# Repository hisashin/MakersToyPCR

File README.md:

## [We're fighting with COVID-19 by upgrading NinjaPCR into affordable Real-Time PCR.](https://github.com/hisashin/NinjaPCR/wiki/NinjaPCR's-fight-with-COVID-19)

NinjaPCR is Opensource(GPLv3) DNA Amplifier,Thermocycler Implementation for [Polymerase Chain Reaction](http://en.wikipedia.org/wiki/Polymerase_chain_reaction) developed by [Shingo Hisakawa](https://www.facebook.com/hisakawa) and [Mariko Hisakawa](https://www.facebook.com/maripo).<br />

Check [support site](https://ninjapcr.tori.st) for more infomations including how to [make](https://ninjapcr.tori.st/maker/) it. BOM is [here](https://docs.google.com/spreadsheets/d/1QYWESJrQ2N63OPvq1pnQvB-iVQkymN-hYeTYLx7xuOw/edit?usp=sharing).

Forked from [OpenPCR](https://github.com/jperfetto/OpenPCR).

Major changes from OpenPCR:<br />
01. Smaller and [easier to build](https://ninjapcr.tori.st/assy/index.html)<br />
02. Change platform from Adobe AIR to WiFi. Almost all PC and smartphones are supported<br />
03. LCD removed. Everything on Browser<br />
04. Keep precision from low to high temperature<br />
05. Auto update for new features (ex. IFTTT support scheduled)<br />
06. It's still [on sale](https://shop.tori.st) (OpenPCR is [discontinued](https://www.chaibio.com/openpcr))

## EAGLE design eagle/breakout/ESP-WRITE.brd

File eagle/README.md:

NinjaPCR PCB
============
[BOM is here](https://docs.google.com/spreadsheets/d/1Eu-5YibDgaByIjIB5OE9yRJ3uC1ED0U484PYJb1YKqg/edit#gid=36)

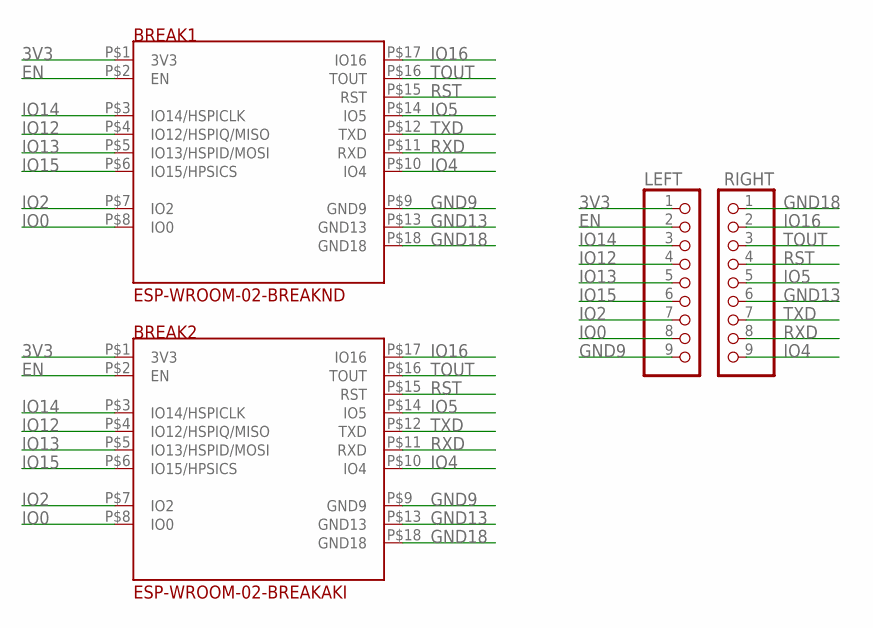
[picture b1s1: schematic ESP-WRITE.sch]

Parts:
BREAK1: ESP-WROOM-02-BREAKND; ESP-WROOM-02-BREAK-NODETAIL
BREAK2: ESP-WROOM-02-BREAKAKI; ESP-WROOM-02-AKI
LEFT: PINHD-1X9; 1X09
RIGHT: PINHD-1X9; 1X09

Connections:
3V3: BREAK1.P$1 (3V3), BREAK2.P$1 (3V3), LEFT.1
EN: BREAK1.P$2 (EN), BREAK2.P$2 (EN), LEFT.2
GND9: BREAK1.P$9 (GND9), BREAK2.P$9 (GND9), LEFT.9
GND13: BREAK1.P$13 (GND13), BREAK2.P$13 (GND13), RIGHT.6
GND18: BREAK1.P$18 (GND18), BREAK2.P$18 (GND18), RIGHT.1
IO0: BREAK1.P$8 (IO0), BREAK2.P$8 (IO0), LEFT.8
IO2: BREAK1.P$7 (IO2), BREAK2.P$7 (IO2), LEFT.7
IO4: BREAK1.P$10 (IO4), BREAK2.P$10 (IO4), RIGHT.9
IO5: BREAK1.P$14 (IO5), BREAK2.P$14 (IO5), RIGHT.5
IO12: BREAK1.P$4 (IO12/HSPIQ/MISO), BREAK2.P$4 (IO12/HSPIQ/MISO), LEFT.4
IO13: BREAK1.P$5 (IO13/HSPID/MOSI), BREAK2.P$5 (IO13/HSPID/MOSI), LEFT.5
IO14: BREAK1.P$3 (IO14/HSPICLK), BREAK2.P$3 (IO14/HSPICLK), LEFT.3
IO15: BREAK1.P$6 (IO15/HPSICS), BREAK2.P$6 (IO15/HPSICS), LEFT.6
IO16: BREAK1.P$17 (IO16), BREAK2.P$17 (IO16), RIGHT.2
RST: BREAK1.P$15 (RST), BREAK2.P$15 (RST), RIGHT.4
RXD: BREAK1.P$11 (RXD), BREAK2.P$11 (RXD), RIGHT.8
TOUT: BREAK1.P$16 (TOUT), BREAK2.P$16 (TOUT), RIGHT.3
TXD: BREAK1.P$12 (TXD), BREAK2.P$12 (TXD), RIGHT.7

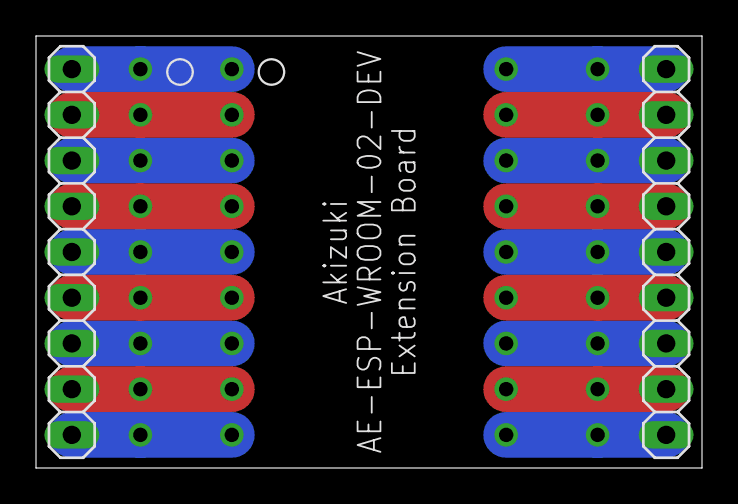
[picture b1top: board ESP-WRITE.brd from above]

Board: 2 copper layers, 37.0 x 24.0 mm, 4 parts (0 on the bottom side), 18 nets.

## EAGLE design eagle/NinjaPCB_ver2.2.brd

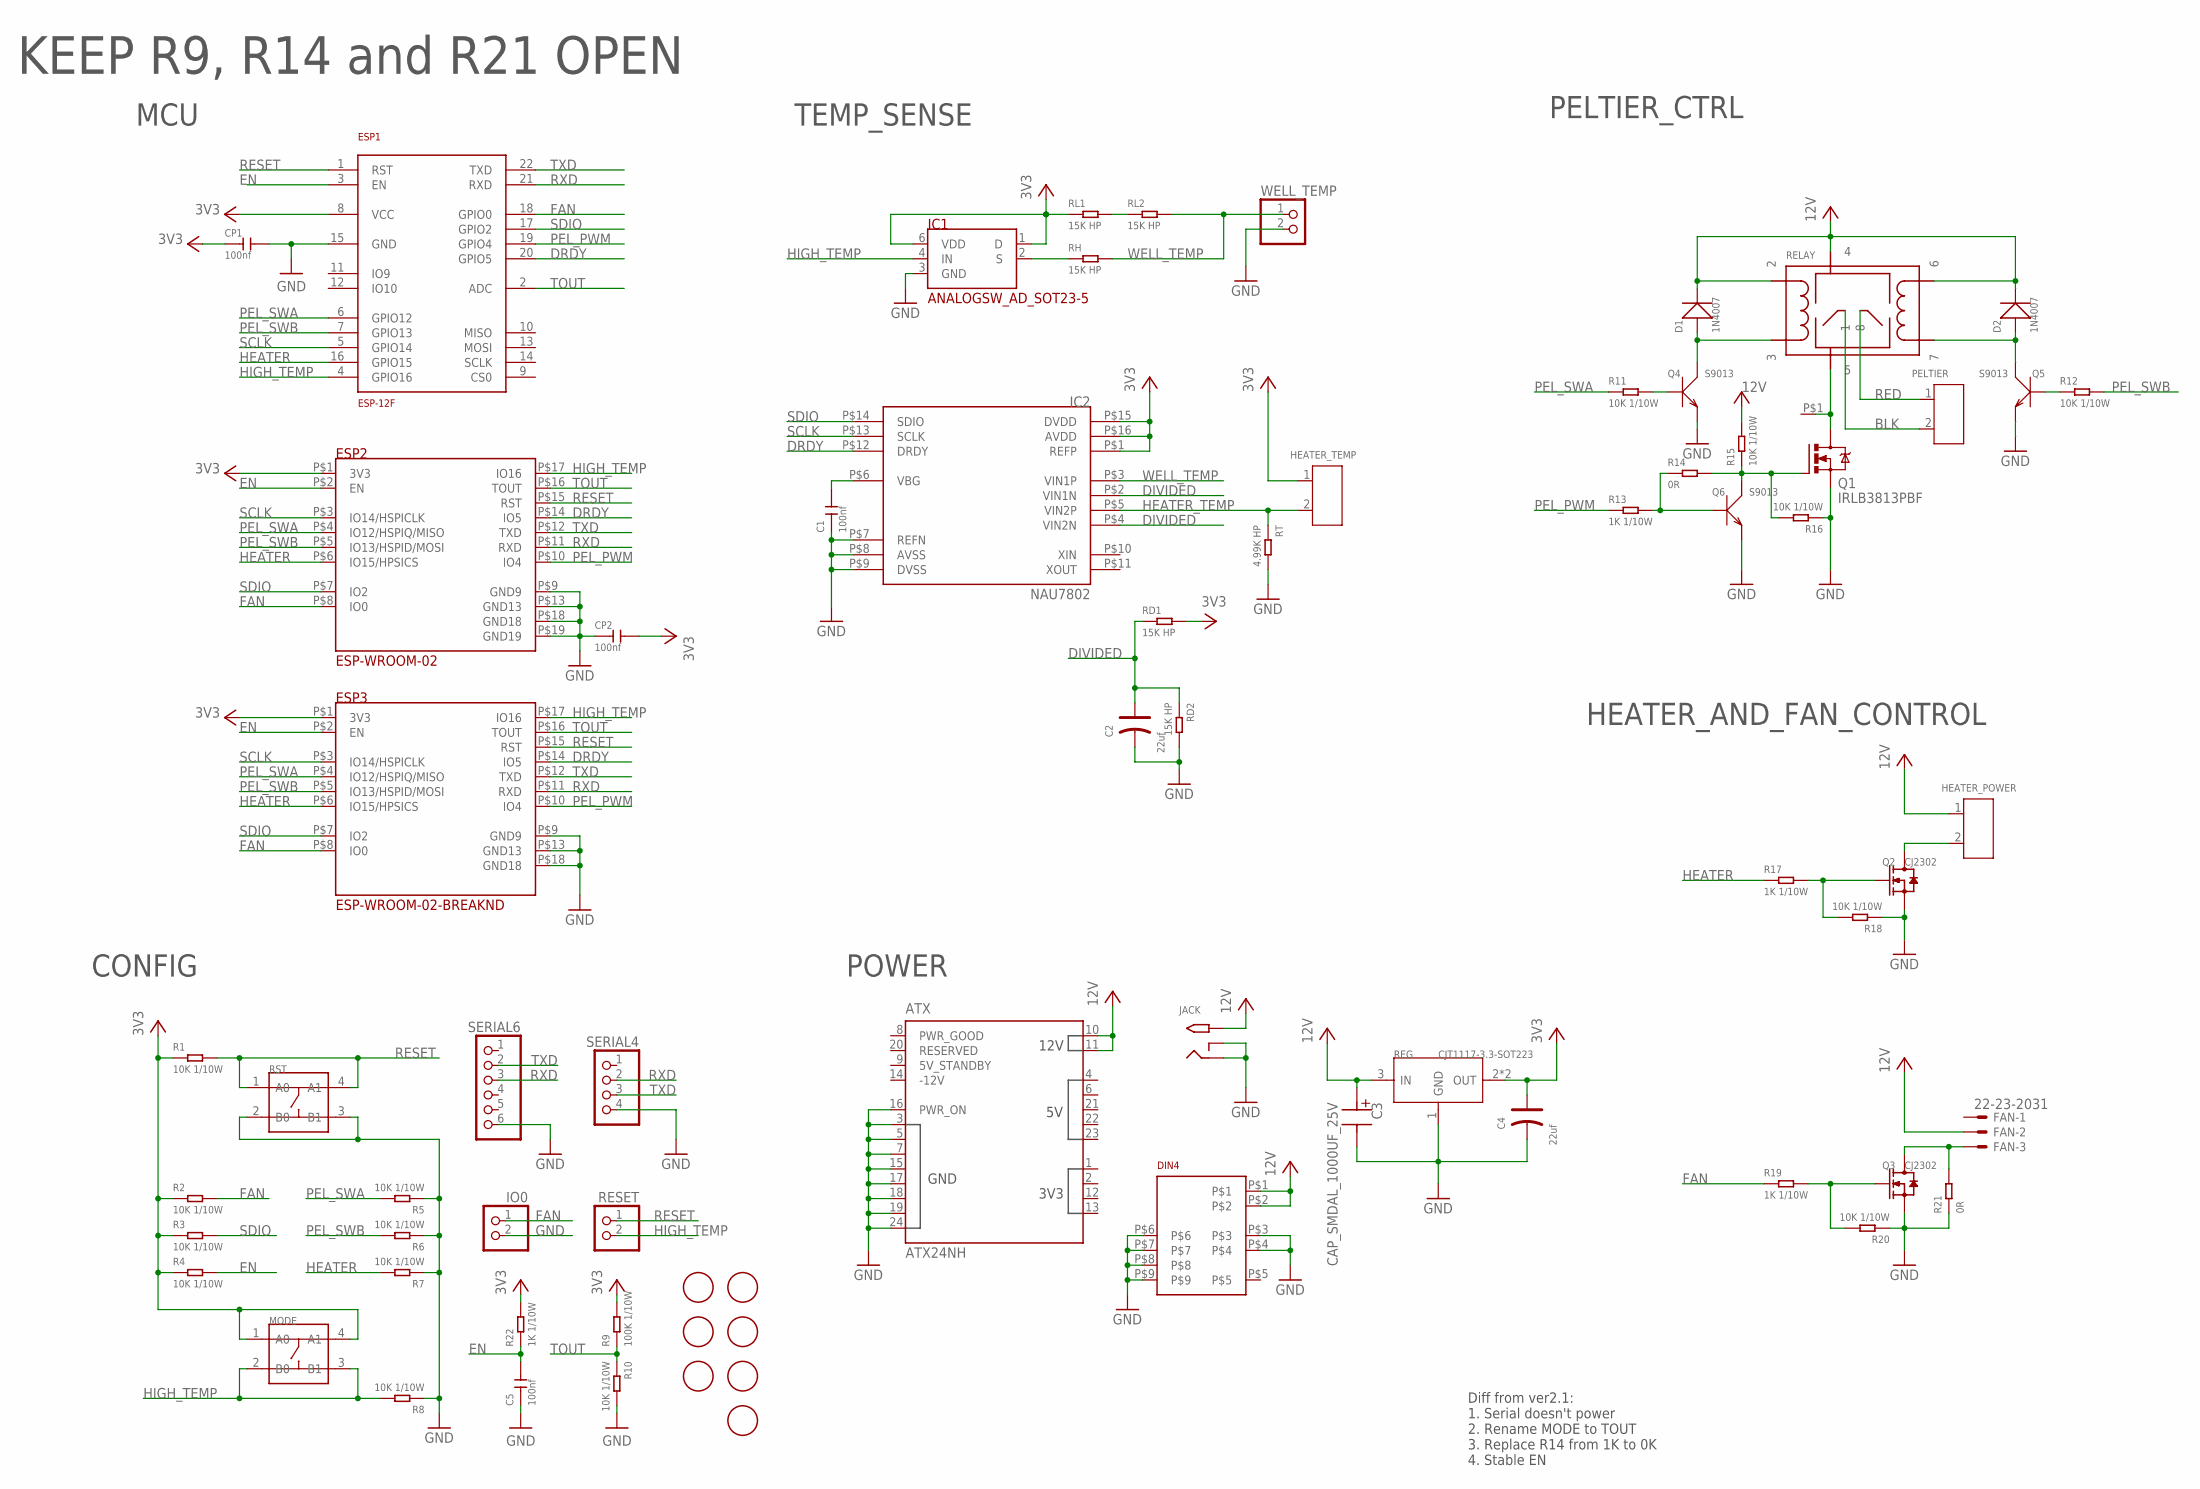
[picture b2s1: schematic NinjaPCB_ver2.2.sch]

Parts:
ATX: ATX24NH; ATX24
C1, C5: 100nf; C0603
C2, C4: 22uf; AVX-B
C3: CAP_SMDAL_1000UF_25V; CAP_SMD_AL_D125
CP1, CP2: 100nf; C0603
D1, D2: 1N4007; DO-214AC
DIN4: DIN4
ESP1: ESP-12F
ESP2: ESP-WROOM-02
ESP3: ESP-WROOM-02-BREAKND; ESP-WROOM-02-BREAK-NODETAIL
FAN: 22-23-2031
HEATER_POWER: SCREW-TERMINAL-GREEN(2P-3.5); H2-3.5-7.0X7.0MM
HEATER_TEMP: SCREW-TERMINAL-GREEN(2P-3.5); H2-3.5-7.0X7.0MM
HEATSINK: HEAT111PB015; HEAT11PB015
IC1: ANALOGSW_AD_SOT23-5; SOT23-5
IC2: NAU7802; SOP-16
IO0: PINHD-1X2; 1X02
JACK: 2.1MMJACKTHM-NOOUT; PJ-102A-NOOUT
MODE: DIP-SWITCH-TACTILE-SPST-NO/TS-1109(4P-D6.0MM)'TS-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; SW4-6.0X6.0X5.0MM
PELTIER: SCREW-TERMINAL-GREEN(2P-3.5); H2-3.5-7.0X7.0MM
Q1: IRLB3813PBF; TO220BV
Q2, Q3: CJ2302; SOT-23
Q4, Q5, Q6: S9013; SOT-23
R1, R2, R3, R4, R5, R6, R7, R8, R10, R11, R12, R15, R16, R18, R20: 10K 1/10W; R0603
R9: 100K 1/10W; R0603
R13, R17, R19, R22: 1K 1/10W; R0603
R14, R21: 0R; R0603
RD1, RD2: 15K HP; R0603
REG: CJT1117-3.3-SOT223; SOT-223
RELAY: NEC-RELAY2EP2; NEC-EP2
RESET: PINHD-1X2; 1X02
RH: 15K HP; R0603
RL1, RL2: 15K HP; R0603
RST: DIP-SWITCH-TACTILE-SPST-NO/TS-1109(4P-D6.0MM)'TS-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; SW4-6.0X6.0X5.0MM
RT: 4.99K HP; R0603
SERIAL4: PINHD-1X4; 1X04
SERIAL6: PINHD-1X6; 1X06
U$3, U$4, U$5, U$7, U$8, U$9, U$10: FIDUCIAL; FIDUCIAL_1MM
WELL_TEMP: PINHD-1X2/90; 1X02/90

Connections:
3V3: C4.+, CP1.1, CP2.2, ESP1.8 (VCC), ESP2.P$1 (3V3), ESP3.P$1 (3V3), HEATER_TEMP.1, IC1.1 (D), IC1.6 (VDD), IC2.P$1 (REFP), IC2.P$15 (DVDD), IC2.P$16 (AVDD), MODE.1 (A0), MODE.4 (A1), R1.1, R2.1, R3.1, R4.1, R9.2, R22.2, RD1.2, REG.2 (OUT), REG.TER (OUT), RL1.1
12V: ATX.10 (12V_10), ATX.11 (12V_11), C3.P$P, D1.2 (-), D2.2 (-), DIN4.P$1, DIN4.P$2, FAN.2, HEATER_POWER.1, JACK.TIP, R15.2, REG.3 (IN), RELAY.P$2 (2), RELAY.P$4 (4), RELAY.P$6 (6)
BLK: PELTIER.2, RELAY.P$1 (1)
DIVIDED: C2.+, IC2.P$2 (VIN1N), IC2.P$4 (VIN2N), RD1.1, RD2.1
DRDY: ESP1.20 (GPIO5), ESP2.P$14 (IO5), ESP3.P$14 (IO5), IC2.P$12 (DRDY)
EN: C5.2, ESP1.3 (EN), ESP2.P$2 (EN), ESP3.P$2 (EN), R4.2, R22.1
FAN: ESP1.18 (GPIO0), ESP2.P$8 (IO0), ESP3.P$8 (IO0), IO0.1, R2.2, R19.1
GND: ATX.3 (GND3), ATX.5 (GND5), ATX.7 (GND7), ATX.15 (GND15), ATX.16 (PWR_ON), ATX.17 (GND17), ATX.18 (GND18), ATX.19 (GND19), ATX.24 (GND24), C1.1, C2.-, C3.P$M, C4.-, C5.1, CP1.2, CP2.1, DIN4.P$3, DIN4.P$4, DIN4.P$6, DIN4.P$7, DIN4.P$8, DIN4.P$9, ESP1.15 (GND), ESP2.P$9 (GND9), ESP2.P$13 (GND13), ESP2.P$18 (GND18), ESP2.P$19 (GND19), ESP3.P$9 (GND9), ESP3.P$13 (GND13), ESP3.P$18 (GND18), IC1.3 (GND), IC2.P$7 (REFN), IC2.P$8 (AVSS), IC2.P$9 (DVSS), IO0.2, JACK.RING, JACK.RING_SW, Q1.S, Q2.2 (S), Q3.2 (S), Q4.2 (E), Q5.2 (E), Q6.2 (E), R5.1, R6.1, R7.1, R8.1, R10.2, R16.1, R18.1, R20.1, R21.1, RD2.2, REG.1 (GND), RST.2 (B0), RST.3 (B1), RT.2, SERIAL4.4, SERIAL6.6, WELL_TEMP.2
HEATER: ESP1.16 (GPIO15), ESP2.P$6 (IO15/HPSICS), ESP3.P$6 (IO15/HPSICS), R7.2, R17.1
HEATER_TEMP: HEATER_TEMP.2, IC2.P$5 (VIN2P), RT.1
HIGH_TEMP: ESP1.4 (GPIO16), ESP2.P$17 (IO16), ESP3.P$17 (IO16), IC1.4 (IN), MODE.2 (B0), MODE.3 (B1), R8.2, RESET.2
unnamed: RL1.2, RL2.1
unnamed: HEATER_POWER.2, Q2.3 (D)
unnamed: HEATSINK.P$1, Q1.D, RELAY.P$5 (5)
unnamed: FAN.3, Q3.3 (D), R21.2
unnamed: Q1.G, Q6.3 (C), R14.2, R15.1, R16.2
unnamed: Q3.1 (G), R19.2, R20.2
unnamed: IC1.2 (S), RH.1
unnamed: Q6.1 (B), R13.2, R14.1
unnamed: Q2.1 (G), R17.2, R18.2
unnamed: D1.1 (+), Q4.3 (C), RELAY.P$3 (3)
unnamed: Q4.1 (B), R11.2
unnamed: Q5.1 (B), R12.1
unnamed: D2.1 (+), Q5.3 (C), RELAY.P$7 (7)
unnamed: C1.2, IC2.P$6 (VBG)
PEL_PWM: ESP1.19 (GPIO4), ESP2.P$10 (IO4), ESP3.P$10 (IO4), R13.1
PEL_SWA: ESP1.6 (GPIO12), ESP2.P$4 (IO12/HSPIQ/MISO), ESP3.P$4 (IO12/HSPIQ/MISO), R5.2, R11.1
PEL_SWB: ESP1.7 (GPIO13), ESP2.P$5 (IO13/HSPID/MOSI), ESP3.P$5 (IO13/HSPID/MOSI), R6.2, R12.2
RED: PELTIER.1, RELAY.P$8 (8)
RESET: ESP1.1 (RST), ESP2.P$15 (RST), ESP3.P$15 (RST), R1.2, RESET.1, RST.1 (A0), RST.4 (A1)
RXD: ESP1.21 (RXD), ESP2.P$11 (RXD), ESP3.P$11 (RXD), SERIAL4.2, SERIAL6.3
SCLK: ESP1.5 (GPIO14), ESP2.P$3 (IO14/HSPICLK), ESP3.P$3 (IO14/HSPICLK), IC2.P$13 (SCLK)
SDIO: ESP1.17 (GPIO2), ESP2.P$7 (IO2), ESP3.P$7 (IO2), IC2.P$14 (SDIO), R3.2
TOUT: ESP1.2 (ADC), ESP2.P$16 (TOUT), ESP3.P$16 (TOUT), R9.1, R10.1
TXD: ESP1.22 (TXD), ESP2.P$12 (TXD), ESP3.P$12 (TXD), SERIAL4.3, SERIAL6.2
WELL_TEMP: IC2.P$3 (VIN1P), RH.2, RL2.2, WELL_TEMP.1

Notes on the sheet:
TEMP_SENSE
HEATER_AND_FAN_CONTROL
PELTIER_CTRL
MCU
POWER
Diff from ver2.1: 1. Serial doesn't power 2. Rename MODE to TOUT 3. Replace R14 from 1K to 0K 4. Stable EN
CONFIG
KEEP R9, R14 and R21 OPEN

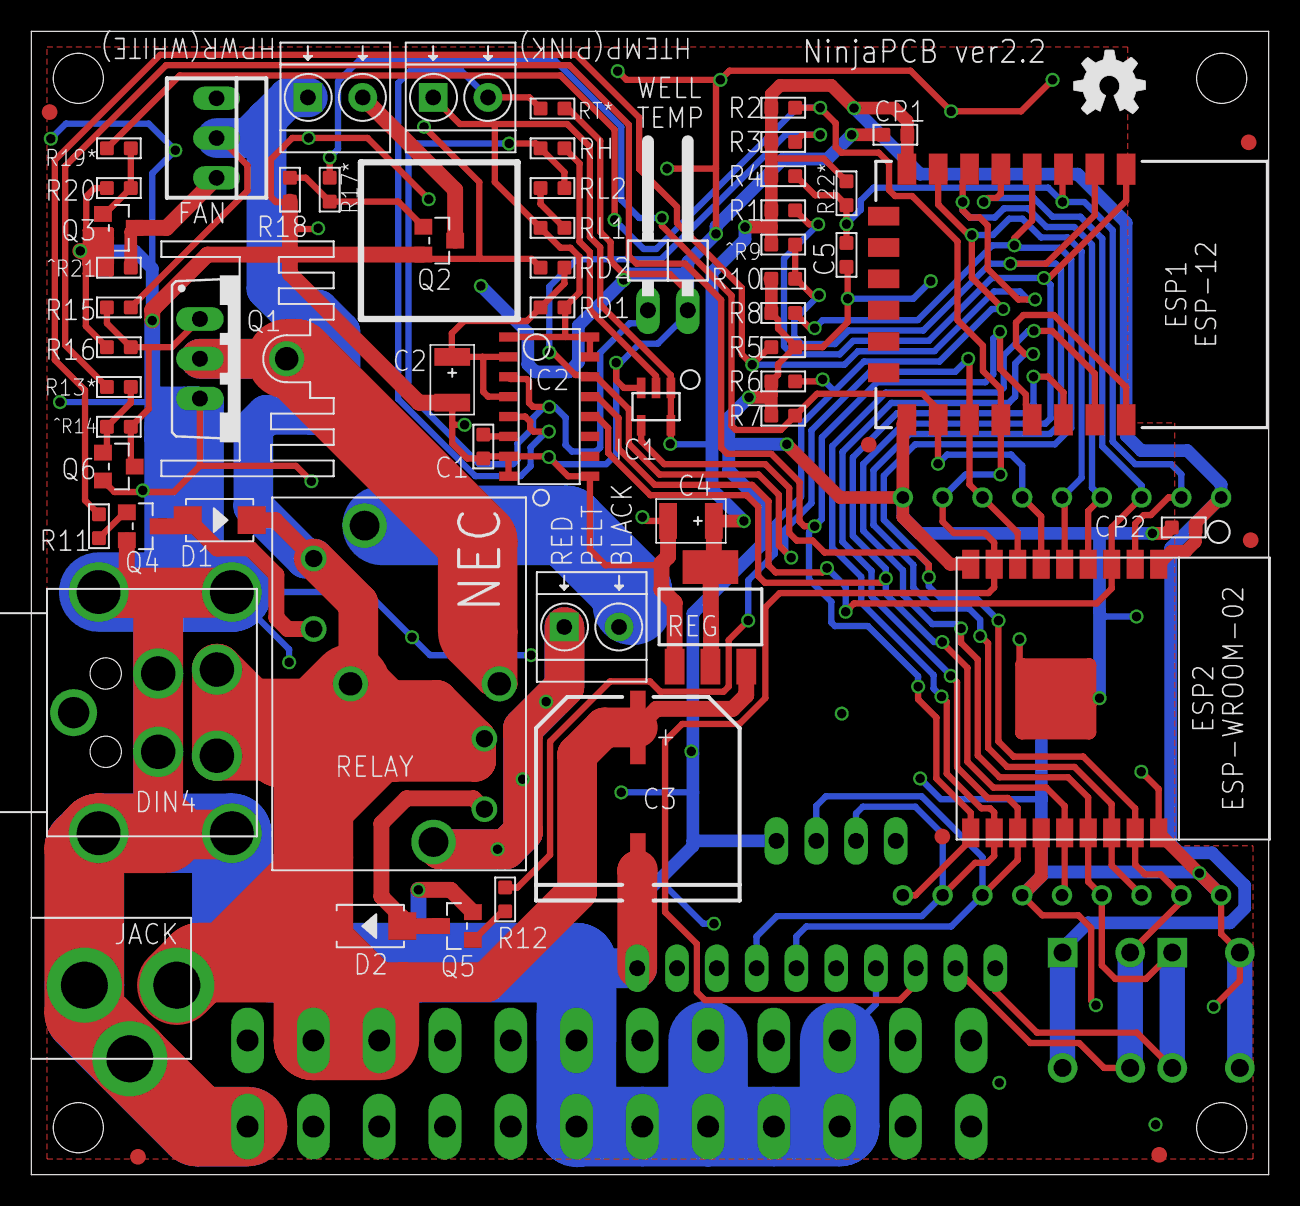
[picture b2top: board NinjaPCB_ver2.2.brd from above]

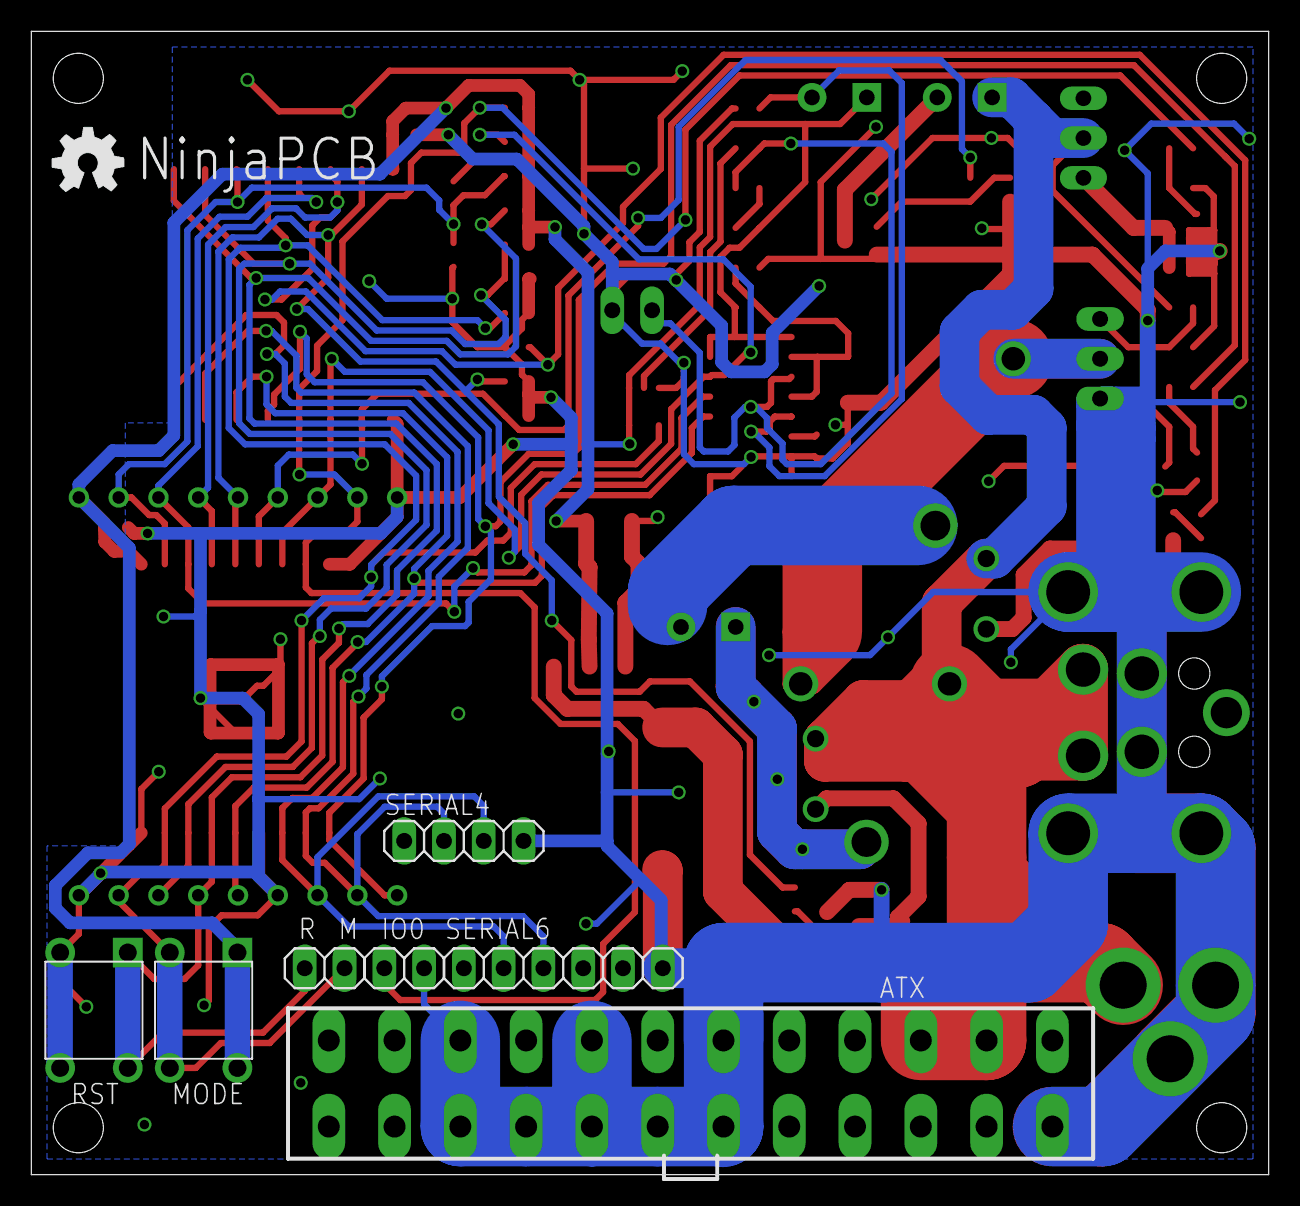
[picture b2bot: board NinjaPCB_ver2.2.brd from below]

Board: 2 copper layers, 79.0 x 73.0 mm, 74 parts (8 on the bottom side), 36 nets.

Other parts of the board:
U$1, U$2: OSHW_5MM

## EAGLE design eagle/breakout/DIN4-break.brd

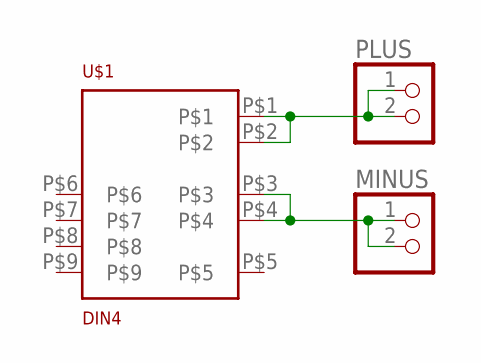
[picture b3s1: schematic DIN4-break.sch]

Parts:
MINUS: PINHD-1X2; 1X02
PLUS: PINHD-1X2; 1X02
U$1: DIN4

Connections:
MINUS: MINUS.1, MINUS.2, U$1.P$3, U$1.P$4
PLUS: PLUS.1, PLUS.2, U$1.P$1, U$1.P$2

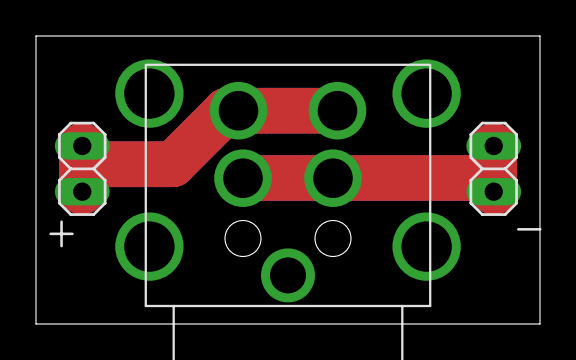
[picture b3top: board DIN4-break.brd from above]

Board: 2 copper layers, 28.0 x 16.0 mm, 3 parts (0 on the bottom side), 2 nets.

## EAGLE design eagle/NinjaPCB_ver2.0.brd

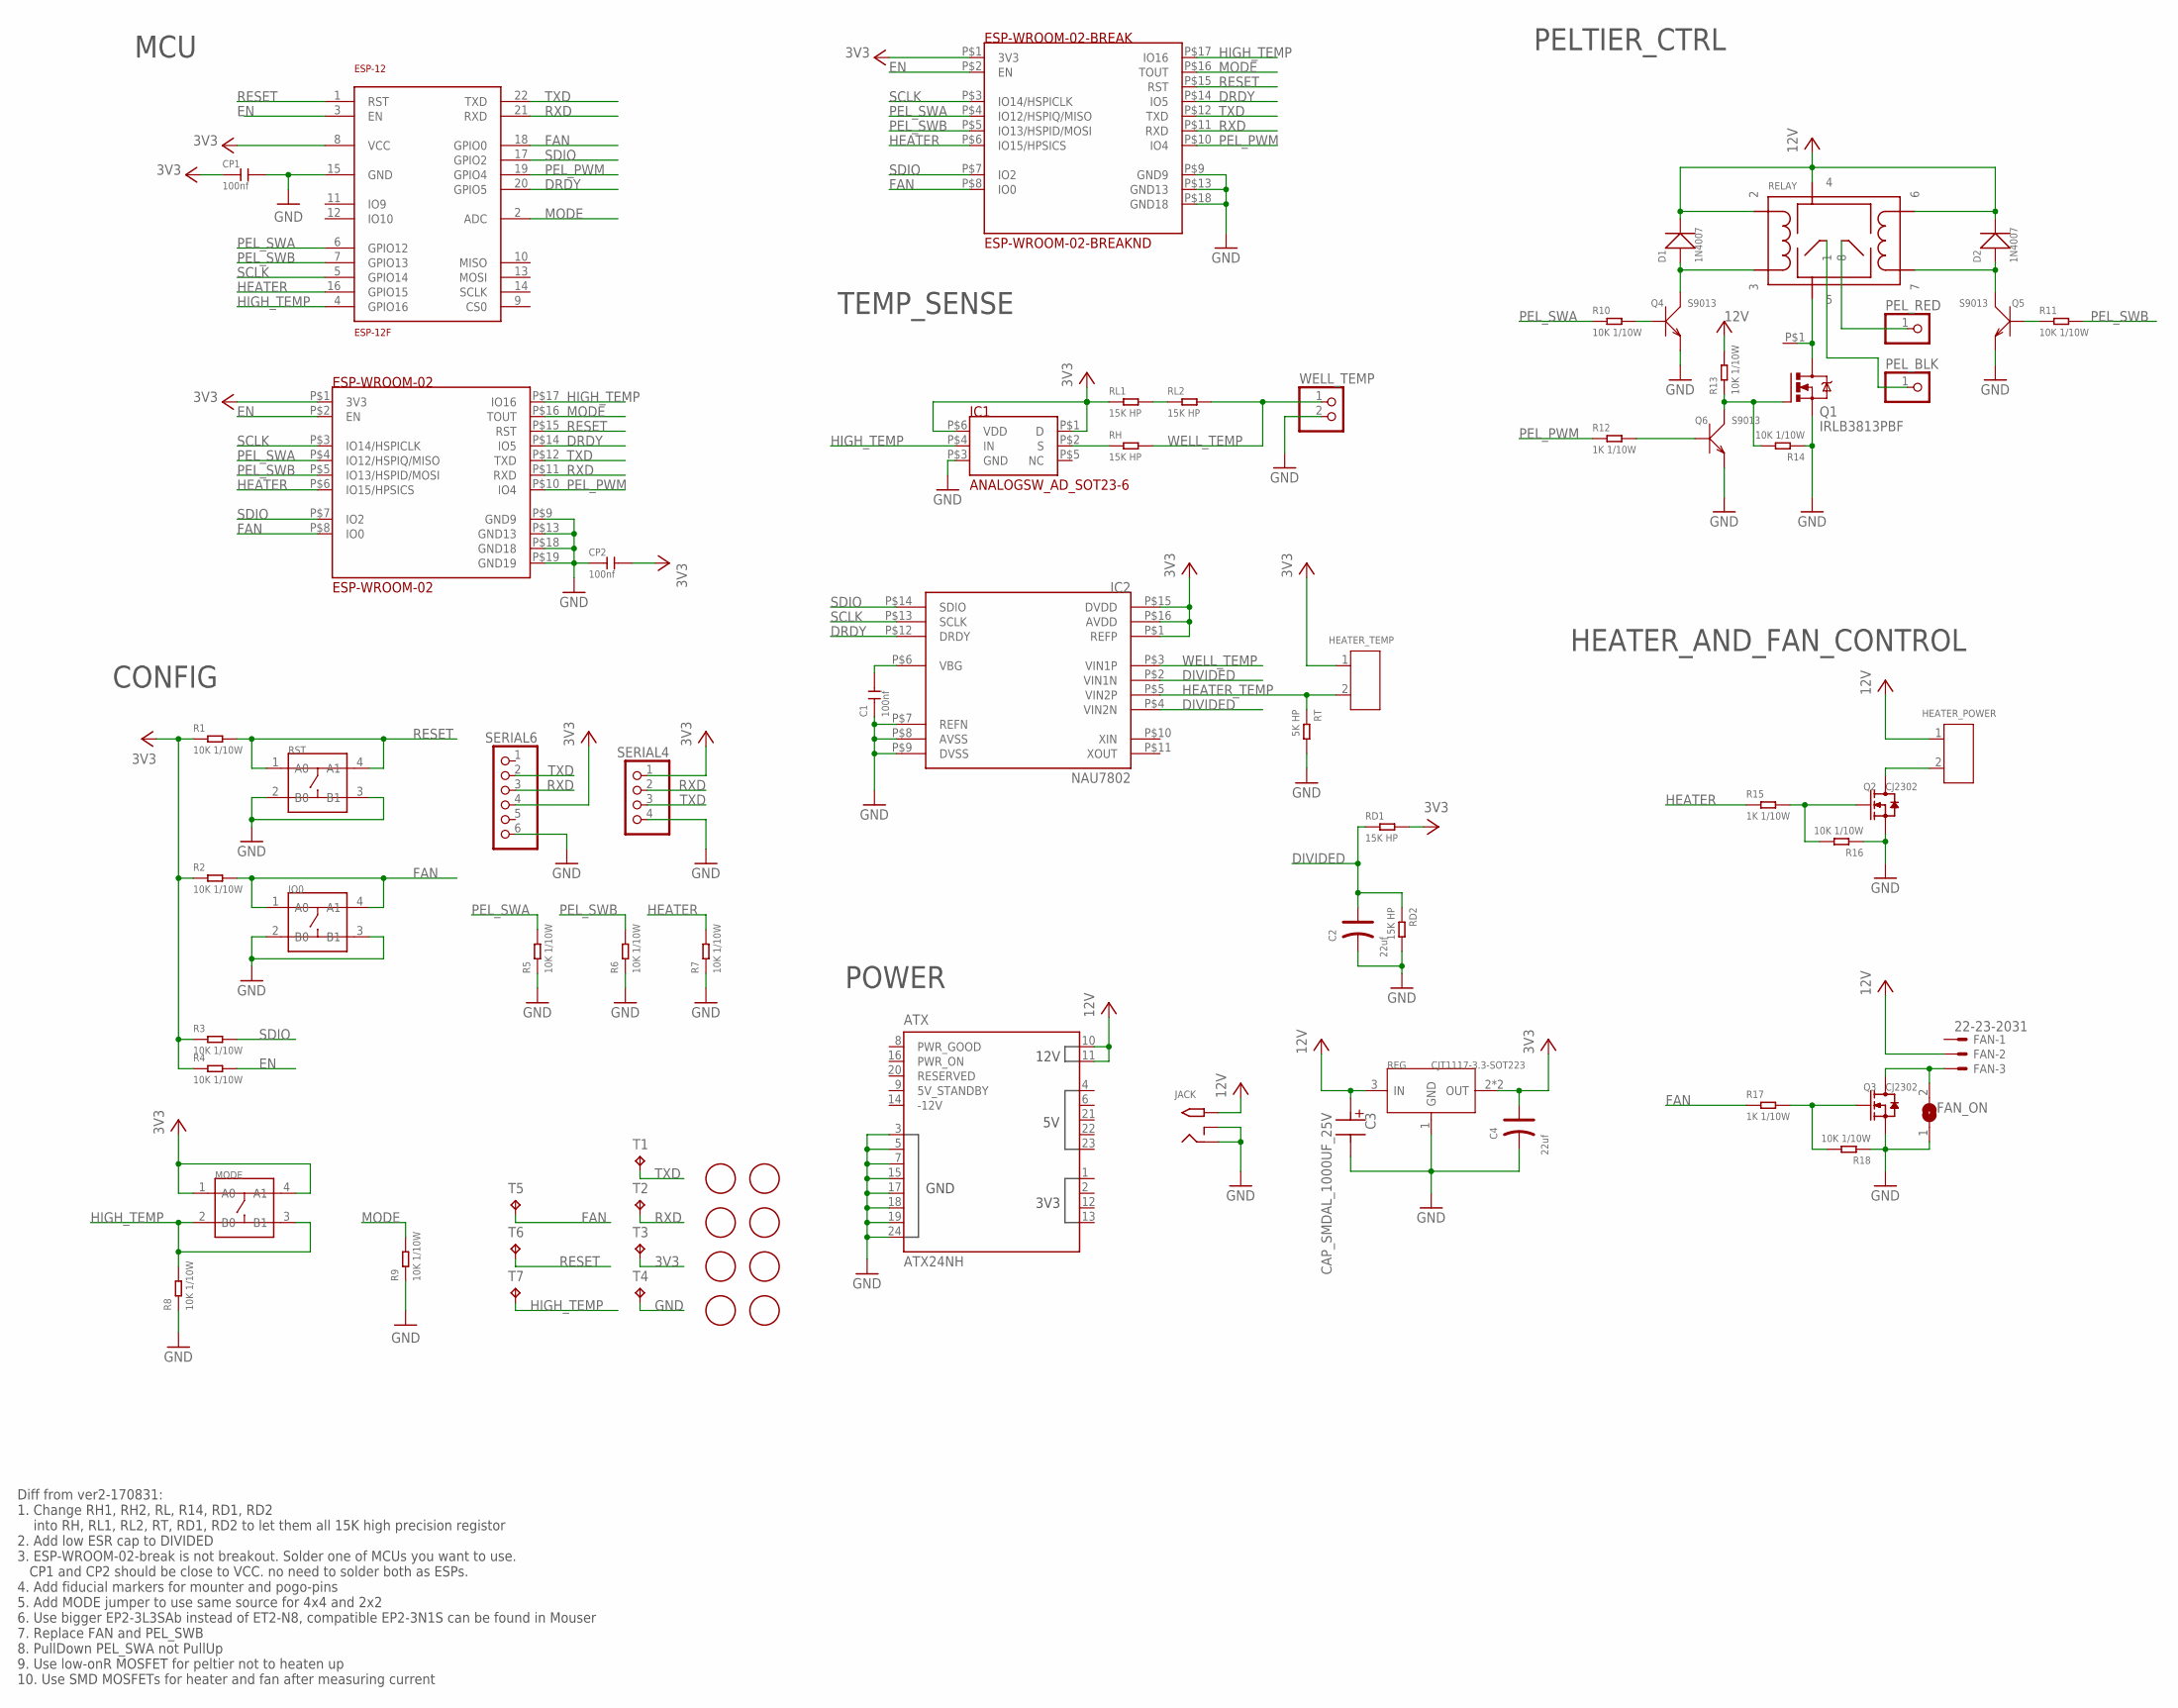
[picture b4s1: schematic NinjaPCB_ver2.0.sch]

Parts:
ATX: ATX24NH; ATX24
C1: 100nf; C0603
C2, C4: 22uf; AVX-B
C3: CAP_SMDAL_1000UF_25V; CAP_SMD_AL_D125
CP1, CP2: 100nf; C0603
D1, D2: 1N4007; DO-214AC
ESP-12: ESP-12F
ESP-WROOM-02: ESP-WROOM-02
ESP-WROOM-02-BREAK: ESP-WROOM-02-BREAKND; ESP-WROOM-02-BREAK-NODETAIL
FAN: 22-23-2031
FAN_ON: SJ
HEATER_POWER: SCREW-TERMINAL-GREEN(2P-3.5); H2-3.5-7.0X7.0MM
HEATER_TEMP: SCREW-TERMINAL-GREEN(2P-3.5); H2-3.5-7.0X7.0MM
HEATSINK: HEAT111PB015; HEAT11PB015
IC1: ANALOGSW_AD_SOT23-6; SOT-23-6
IC2: NAU7802; SOP-16
IO0: DIP-SWITCH-TACTILE-SPST-NO/TS-1109(4P-D6.0MM)'TS-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; SW4-6.0X6.0X5.0MM
JACK: 2.1MMJACKTHM-NOOUT; PJ-102A-NOOUT
MODE: DIP-SWITCH-TACTILE-SPST-NO/TS-1109(4P-D6.0MM)'TS-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; SW4-6.0X6.0X5.0MM
PEL_BLK: PINHD-1X1L; 1X01LONG
PEL_RED: PINHD-1X1L; 1X01LONG
Q1: IRLB3813PBF; TO220BV
Q2, Q3: CJ2302; SOT-23
Q4, Q5, Q6: S9013; SOT-23
R1, R2, R3, R4, R5, R6, R7, R8, R9, R10, R11, R13, R14, R16, R18: 10K 1/10W; R0603
R12, R15, R17: 1K 1/10W; R0603
RD1, RD2: 15K HP; R0603
REG: CJT1117-3.3-SOT223; SOT-223
RELAY: NEC-RELAY2EN2; NEC-EN2
RH: 15K HP; R0603
RL1, RL2: 15K HP; R0603
RST: DIP-SWITCH-TACTILE-SPST-NO/TS-1109(4P-D6.0MM)'TS-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; SW4-6.0X6.0X5.0MM
RT: 5K HP; R0603
SERIAL4: PINHD-1X4; 1X04
SERIAL6: PINHD-1X6; 1X06
T1, T2, T3, T4, T5, T6, T7: TPTP20R; TP20R
U$3, U$4, U$5, U$6, U$7, U$8, U$9, U$10: FIDUCIAL; FIDUCIAL_1MM
WELL_TEMP: PINHD-1X2; 1X02

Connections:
3V3: C4.+, CP1.1, CP2.2, ESP-12.8 (VCC), ESP-WROOM-02.P$1 (3V3), ESP-WROOM-02-BREAK.P$1 (3V3), HEATER_TEMP.1, IC1.P$1 (D), IC1.P$6 (VDD), IC2.P$1 (REFP), IC2.P$15 (DVDD), IC2.P$16 (AVDD), MODE.1 (A0), MODE.4 (A1), R1.1, R2.1, R3.1, R4.1, RD1.2, REG.2 (OUT), REG.TER (OUT), RL1.1, SERIAL4.1, SERIAL6.4, T3.TP
12V: ATX.10 (12V_10), ATX.11 (12V_11), C3.P$P, D1.2 (-), D2.2 (-), FAN.2, HEATER_POWER.1, JACK.TIP, R13.2, REG.3 (IN), RELAY.P$2 (2), RELAY.P$4 (4), RELAY.P$6 (6)
DIVIDED: C2.+, IC2.P$2 (VIN1N), IC2.P$4 (VIN2N), RD1.1, RD2.1
DRDY: ESP-12.20 (GPIO5), ESP-WROOM-02.P$14 (IO5), ESP-WROOM-02-BREAK.P$14 (IO5), IC2.P$12 (DRDY)
EN: ESP-12.3 (EN), ESP-WROOM-02.P$2 (EN), ESP-WROOM-02-BREAK.P$2 (EN), R4.2
FAN: ESP-12.18 (GPIO0), ESP-WROOM-02.P$8 (IO0), ESP-WROOM-02-BREAK.P$8 (IO0), IO0.1 (A0), IO0.4 (A1), R2.2, R17.1, T5.TP
GND: ATX.3 (GND3), ATX.5 (GND5), ATX.7 (GND7), ATX.15 (GND15), ATX.17 (GND17), ATX.18 (GND18), ATX.19 (GND19), ATX.24 (GND24), C1.1, C2.-, C3.P$M, C4.-, CP1.2, CP2.1, ESP-12.15 (GND), ESP-WROOM-02.P$9 (GND9), ESP-WROOM-02.P$13 (GND13), ESP-WROOM-02.P$18 (GND18), ESP-WROOM-02.P$19 (GND19), ESP-WROOM-02-BREAK.P$9 (GND9), ESP-WROOM-02-BREAK.P$13 (GND13), ESP-WROOM-02-BREAK.P$18 (GND18), FAN_ON.1, IC1.P$3 (GND), IC2.P$7 (REFN), IC2.P$8 (AVSS), IC2.P$9 (DVSS), IO0.2 (B0), IO0.3 (B1), JACK.RING, JACK.RING_SW, Q1.S, Q2.2 (S), Q3.2 (S), Q4.2 (E), Q5.2 (E), Q6.2 (E), R5.1, R6.1, R7.1, R8.1, R9.1, R14.1, R16.1, R18.1, RD2.2, REG.1 (GND), RST.2 (B0), RST.3 (B1), RT.2, SERIAL4.4, SERIAL6.6, T4.TP, WELL_TEMP.2
HEATER: ESP-12.16 (GPIO15), ESP-WROOM-02.P$6 (IO15/HPSICS), ESP-WROOM-02-BREAK.P$6 (IO15/HPSICS), R7.2, R15.1
HEATER_TEMP: HEATER_TEMP.2, IC2.P$5 (VIN2P), RT.1
HIGH_TEMP: ESP-12.4 (GPIO16), ESP-WROOM-02.P$17 (IO16), ESP-WROOM-02-BREAK.P$17 (IO16), IC1.P$4 (IN), MODE.2 (B0), MODE.3 (B1), R8.2, T7.TP
MODE: ESP-12.2 (ADC), ESP-WROOM-02.P$16 (TOUT), ESP-WROOM-02-BREAK.P$16 (TOUT), R9.2
unnamed: RL1.2, RL2.1
unnamed: HEATER_POWER.2, Q2.3 (D)
unnamed: HEATSINK.P$1, Q1.D, RELAY.P$5 (5)
unnamed: FAN.3, FAN_ON.2, Q3.3 (D)
unnamed: Q1.G, Q6.3 (C), R13.1, R14.2
unnamed: PEL_RED.1, RELAY.P$8 (8)
unnamed: PEL_BLK.1, RELAY.P$1 (1)
unnamed: Q3.1 (G), R17.2, R18.2
unnamed: IC1.P$2 (S), RH.1
unnamed: Q6.1 (B), R12.2
unnamed: Q2.1 (G), R15.2, R16.2
unnamed: D1.1 (+), Q4.3 (C), RELAY.P$3 (3)
unnamed: Q4.1 (B), R10.2
unnamed: Q5.1 (B), R11.1
unnamed: D2.1 (+), Q5.3 (C), RELAY.P$7 (7)
unnamed: C1.2, IC2.P$6 (VBG)
PEL_PWM: ESP-12.19 (GPIO4), ESP-WROOM-02.P$10 (IO4), ESP-WROOM-02-BREAK.P$10 (IO4), R12.1
PEL_SWA: ESP-12.6 (GPIO12), ESP-WROOM-02.P$4 (IO12/HSPIQ/MISO), ESP-WROOM-02-BREAK.P$4 (IO12/HSPIQ/MISO), R5.2, R10.1
PEL_SWB: ESP-12.7 (GPIO13), ESP-WROOM-02.P$5 (IO13/HSPID/MOSI), ESP-WROOM-02-BREAK.P$5 (IO13/HSPID/MOSI), R6.2, R11.2
RESET: ESP-12.1 (RST), ESP-WROOM-02.P$15 (RST), ESP-WROOM-02-BREAK.P$15 (RST), R1.2, RST.1 (A0), RST.4 (A1), T6.TP
RXD: ESP-12.21 (RXD), ESP-WROOM-02.P$11 (RXD), ESP-WROOM-02-BREAK.P$11 (RXD), SERIAL4.2, SERIAL6.3, T2.TP
SCLK: ESP-12.5 (GPIO14), ESP-WROOM-02.P$3 (IO14/HSPICLK), ESP-WROOM-02-BREAK.P$3 (IO14/HSPICLK), IC2.P$13 (SCLK)
SDIO: ESP-12.17 (GPIO2), ESP-WROOM-02.P$7 (IO2), ESP-WROOM-02-BREAK.P$7 (IO2), IC2.P$14 (SDIO), R3.2
TXD: ESP-12.22 (TXD), ESP-WROOM-02.P$12 (TXD), ESP-WROOM-02-BREAK.P$12 (TXD), SERIAL4.3, SERIAL6.2, T1.TP
WELL_TEMP: IC2.P$3 (VIN1P), RH.2, RL2.2, WELL_TEMP.1

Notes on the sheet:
TEMP_SENSE
HEATER_AND_FAN_CONTROL
PELTIER_CTRL
MCU
POWER
Diff from ver2-170831: 1. Change RH1, RH2, RL, R14, RD1, RD2 into RH, RL1, RL2, RT, RD1, RD2 to let them all 15K high precision registor 2. Add low ESR cap to DIVIDED 3. ESP-WROOM-02-break is not breakout. Solder one of MCUs you want to use. CP1 and CP2 should be close to VCC. no need to solder bot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
CONFIG

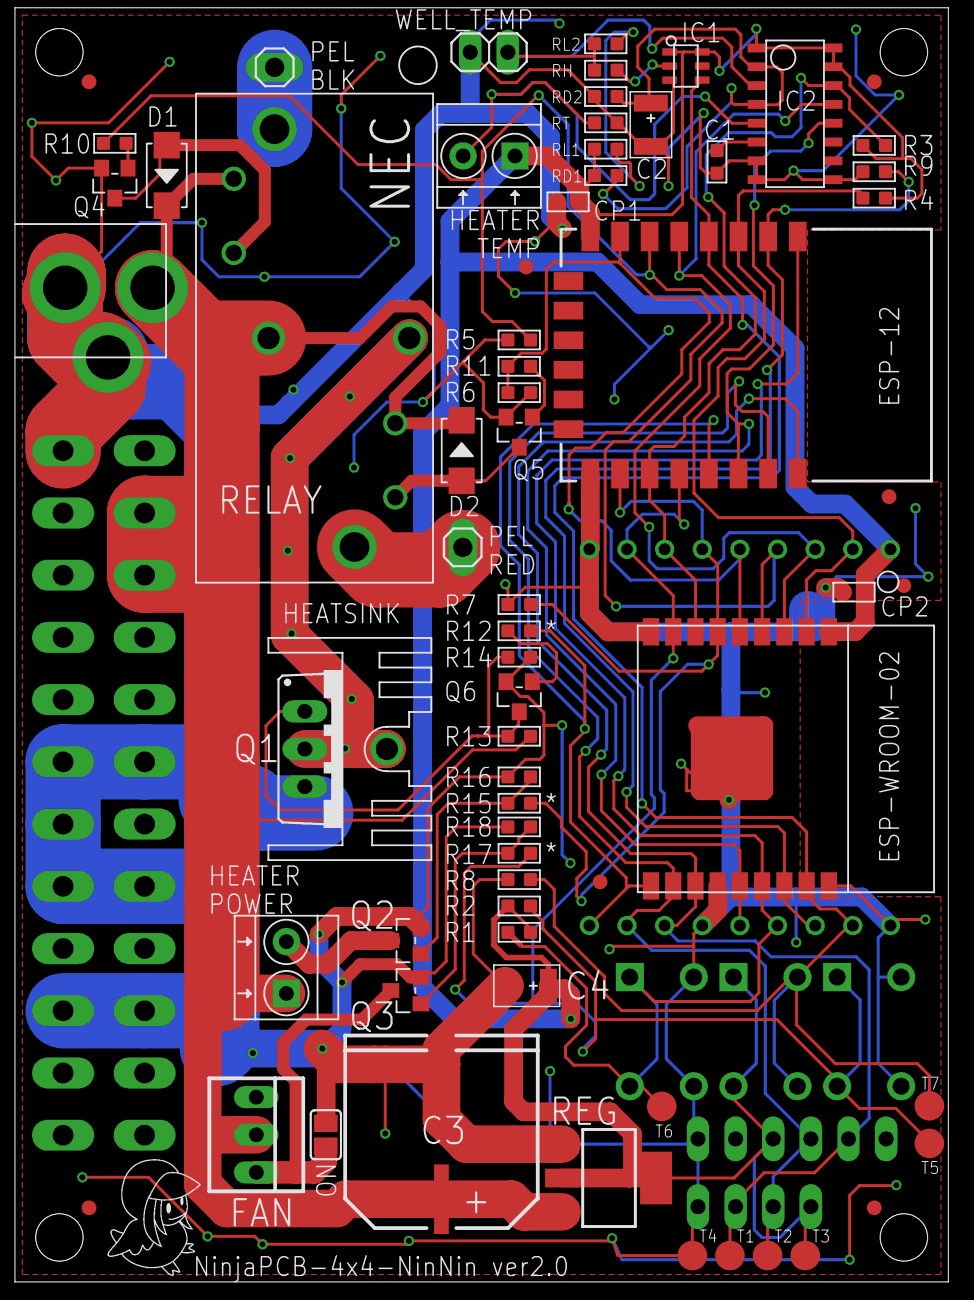
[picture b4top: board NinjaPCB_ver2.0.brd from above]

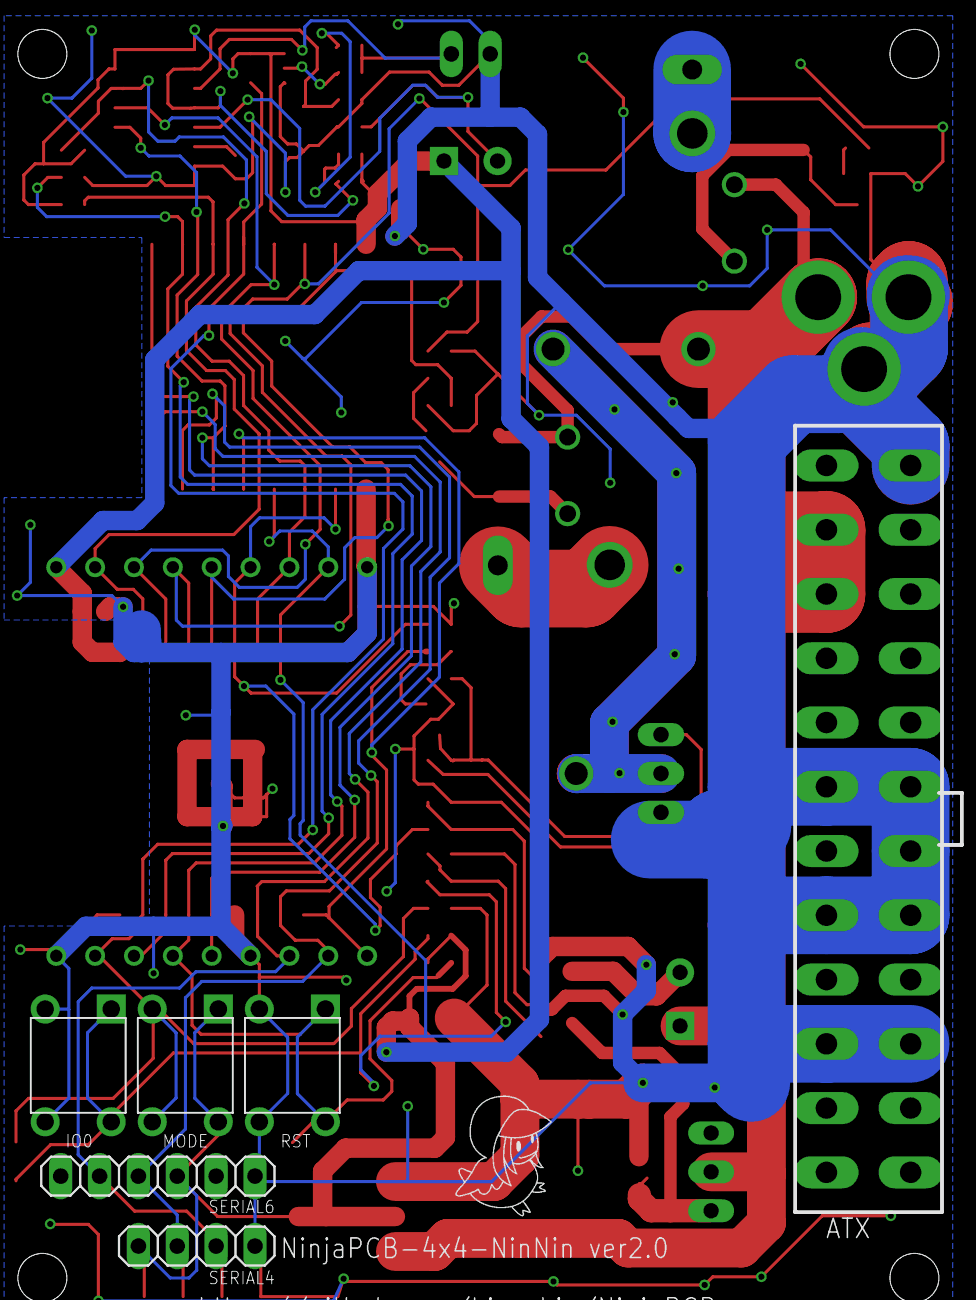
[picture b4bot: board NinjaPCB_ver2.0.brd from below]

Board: 2 copper layers, 77 parts (7 on the bottom side), 36 nets.

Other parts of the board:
U$1, U$2: TORI_0.25

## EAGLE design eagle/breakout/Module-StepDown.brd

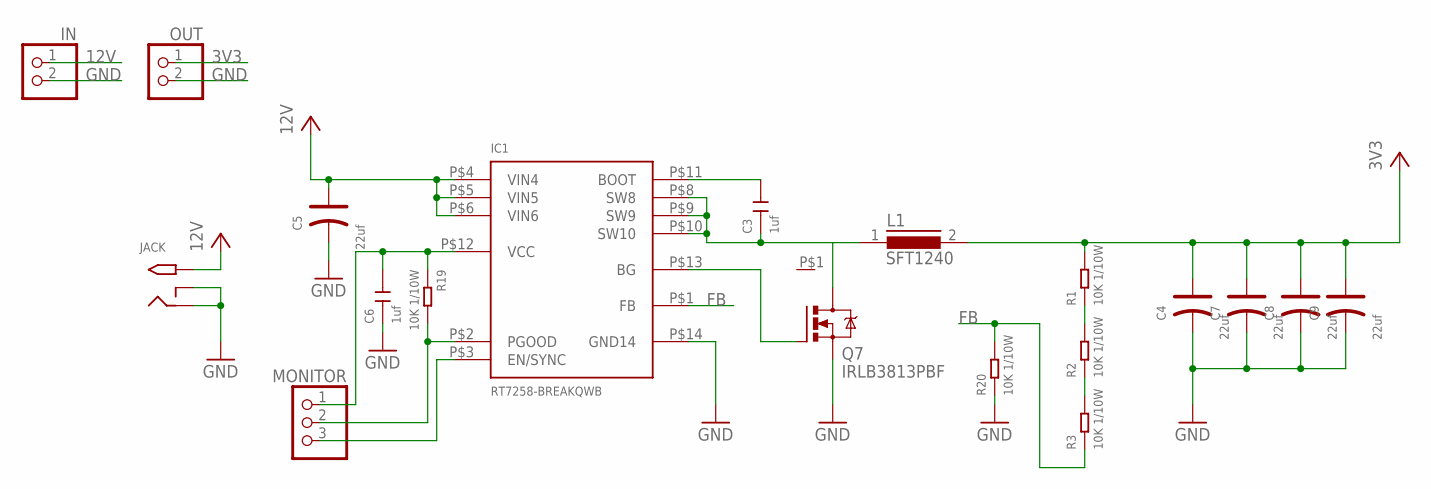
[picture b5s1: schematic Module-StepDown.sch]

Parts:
C3, C6: 1uf; C0603
C4, C5, C7, C8, C9: 22uf; AVX-B
HEATSINK1: HEAT111PB015; HEAT11PB015
IC1: RT7258-BREAKQWB; RT7258GQW-BREAK
IN: PINHD-1X2; 1X02
JACK: 2.1MMJACKTHM-NOOUT; PJ-102A-NOOUT
L1: SFT1240
MONITOR: PINHD-1X3; 1X03
OUT: PINHD-1X2; 1X02
Q7: IRLB3813PBF; TO220BV
R1, R2, R3, R19, R20: 10K 1/10W; R0603

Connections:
3V3: C4.+, C7.+, C8.+, C9.+, L1.2, OUT.1, R1.2
12V: C5.+, IC1.P$4 (VIN4), IC1.P$5 (VIN5), IC1.P$6 (VIN6), IN.1, JACK.TIP
EN/SYNC: IC1.P$3 (EN/SYNC), MONITOR.3
FB: IC1.P$1 (FB), R3.1, R20.2
GND: C4.-, C5.-, C6.1, C7.-, C8.-, C9.-, IC1.P$14 (GND14), IN.2, JACK.RING, JACK.RING_SW, OUT.2, Q7.S, R20.1
unnamed: R2.1, R3.2
unnamed: R1.1, R2.2
unnamed: C3.2, IC1.P$11 (BOOT)
unnamed: IC1.P$13 (BG), Q7.G
PGOOD: IC1.P$2 (PGOOD), MONITOR.2, R19.2
SW: C3.1, IC1.P$8 (SW8), IC1.P$9 (SW9), IC1.P$10 (SW10), L1.1, Q7.D
VCC: C6.2, IC1.P$12 (VCC), MONITOR.1, R19.1
